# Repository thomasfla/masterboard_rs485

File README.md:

# masterboard_rs485
Robot central board with ESP32 + RP2040 + 4 RS485 half duplex Tranceivers

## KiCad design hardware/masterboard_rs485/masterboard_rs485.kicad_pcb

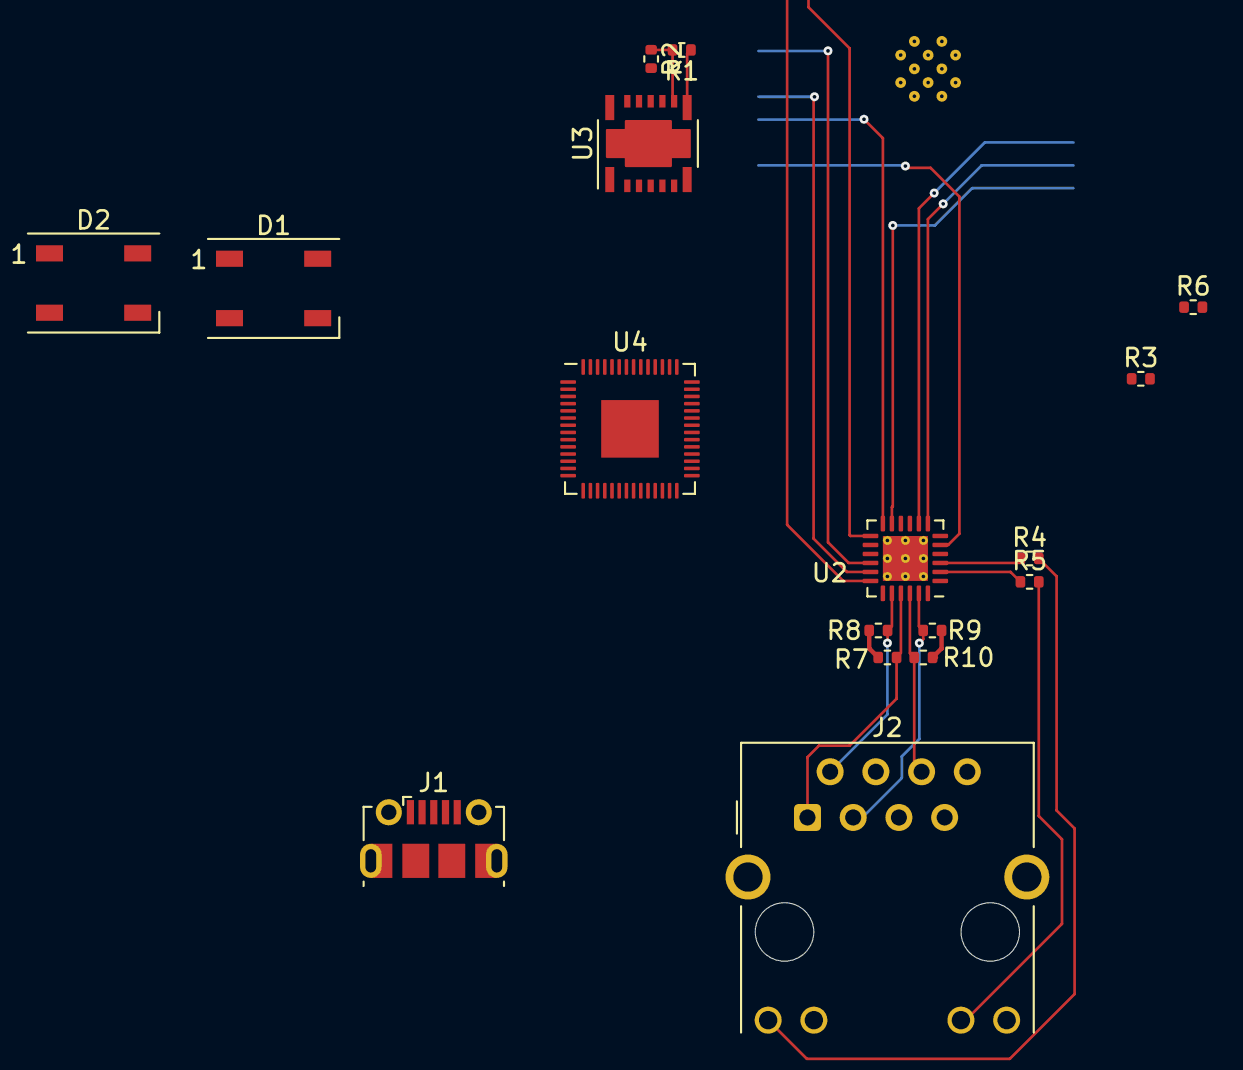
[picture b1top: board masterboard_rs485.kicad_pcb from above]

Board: 2 copper layers, 18 parts (1 on the bottom side), 30 nets.

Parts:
D1, D2: WS2812B; LED_WS2812B_PLCC4_5.0x5.0mm_P3.2mm
J1: USB_B_Micro; USB_Micro-B_Molex-105017-0001
J2: RJ45_LED_Shielded; RJ45_Hanrun_HR911105A_Horizontal
R1, R2, R3, R4, R5, R6: R; R_0402_1005Metric
R7, R8, R9, R10: 49.9; R_0402_1005Metric
U1: ESP32-WROOM-32
U2: LAN8720A; VQFN-24-1EP_4x4mm_P0.5mm_EP2.5x2.5mm_ThermalVias
U3: TPSM560R6; B3QFN_15
U4: RP2040; QFN-56-1EP_7x7mm_P0.4mm_EP3.2x3.2mm

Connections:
+3V3: D1.1 (VDD), D2.1 (VDD), J2.4, J2.5, J2.10, J2.12, R7.2, R8.2, R9.2, R10.2, U1.2 (VDD), U2.1 (VDD2A), U2.9 (VDDIO), U2.10 (RXER/PHYAD0), U2.19 (VDD1A)
/CLK50: U1.28 (IO17), U2.5 (XTAL1/CLKIN)
/CRS: U1.12 (IO27), U2.11 (CRS_DV/MODE2)
/IO2: D1.4 (DIN), U1.24 (IO2)
/MDC: U1.37 (IO23), U2.13 (MDC)
/MDIO: U1.30 (IO18), U2.12 (MDIO)
/RXD0: U1.10 (IO25), U2.8 (RXD0/MODE0)
/RXD1: U1.11 (IO26), U2.7 (RXD1/MODE1)
/TXD0: U1.31 (IO19), U2.17 (TXD0)
/TXD1: U1.36 (IO22), U2.18 (TXD1)
/TX_EN: U1.33 (IO21), U2.16 (TXEN)
/VIN: U3.1 (Vin), U3.2 (EN), U3.14 (Vin)
GND: D1.3 (VSS), D2.3 (VSS), J2.8, J2.SH, R2.2, R6.2, U1.1 (GND), U1.15 (GND), U1.38 (GND), U1.39 (GND), U2.25 (VSS), U3.10 (AGND), U3.15 (PGND)
unnamed: R1.1, R3.1, U3.7 (Vout), U3.8 (Vout)
unnamed: D1.2 (DOUT), D2.4 (DIN)
unnamed: J1.3 (D+), U4.47 (USB_DP)
unnamed: J1.2 (D-), U4.46 (USB_DM)
unnamed: J2.9, R4.2
unnamed: J2.11, R5.2
unnamed: R4.1, U2.3 (LED1/REGOFF)
unnamed: R5.1, U2.2 (LED2/~INTSEL)
unnamed: R6.1, U2.24 (RBIAS)
unnamed: J2.6, R10.1, U2.22 (RXN)
unnamed: J2.3, R9.1, U2.23 (RXP)
unnamed: J2.2, R8.1, U2.20 (TXN)
unnamed: J2.1, R7.1, U2.21 (TXP)
unnamed: R1.2, R2.1, U3.9 (FB)
unnamed: R3.2, U3.12 (PG)
unnamed: U4.23 (DVDD), U4.50 (DVDD)
unnamed: U4.1 (IOVDD), U4.10 (IOVDD), U4.22 (IOVDD), U4.33 (IOVDD), U4.42 (IOVDD), U4.49 (IOVDD)

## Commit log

2023-11-23 first hardware draft
